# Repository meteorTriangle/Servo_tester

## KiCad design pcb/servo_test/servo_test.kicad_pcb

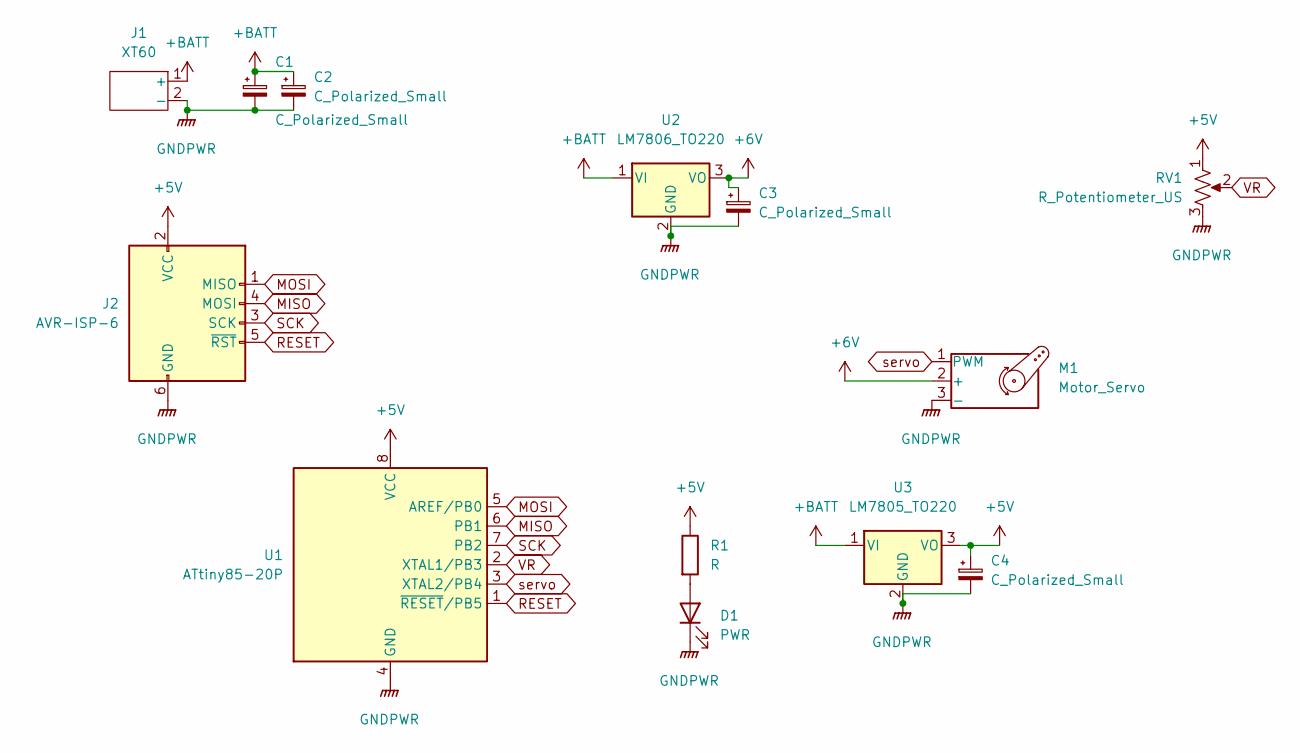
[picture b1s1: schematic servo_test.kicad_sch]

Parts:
C1, C2, C3, C4: C_Polarized_Small; CP_Radial_D5.0mm_P2.00mm
D1: PWR; LED_0805_2012Metric
J1: XT60; XT60_vertical_female
J2: AVR-ISP-6; PinHeader_2x03_P2.54mm_Vertical
M1: Motor_Servo; PinHeader_1x03_P2.54mm_Vertical
R1: R; R_0805_2012Metric
RV1: R_Potentiometer_US; Potentiometer_Piher_PC-16_Single_Horizontal
U1: ATtiny85-20P; DIP-8_W7.62mm
U2: LM7806_TO220; TO-220-3_Vertical
U3: LM7805_TO220; TO-220-3_Vertical

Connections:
+5V: C4.1, J2.2 (VCC), R1.1, RV1.1, U1.8 (VCC), U3.3 (VO)
+6V: C3.1, M1.2 (+), U2.3 (VO)
+BATT: C1.1, C2.1, J1.1 (+), U2.1 (VI), U3.1 (VI)
GNDPWR: C1.2, C2.2, C3.2, C4.2, D1.1 (K), J1.2 (-), J2.6 (GND), M1.3 (-), RV1.3, U1.4 (GND), U2.2 (GND), U3.2 (GND)
MISO: J2.4 (MOSI), U1.6 (PB1)
MOSI: J2.1 (MISO), U1.5 (AREF/PB0)
unnamed: D1.2 (A), R1.2
RESET: J2.5 (~RST), U1.1 (~RESET/PB5)
SCK: J2.3 (SCK), U1.7 (PB2)
VR: RV1.2, U1.2 (XTAL1/PB3)
servo: M1.1 (PWM), U1.3 (XTAL2/PB4)

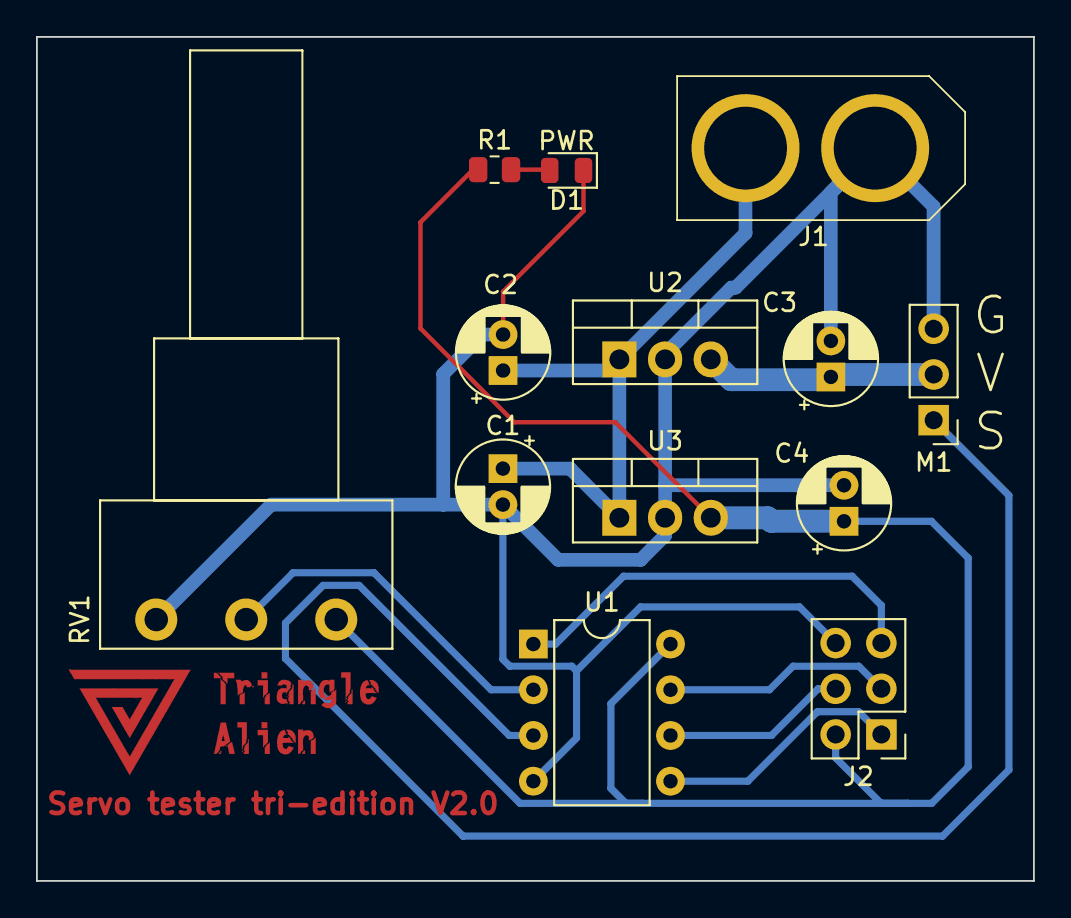
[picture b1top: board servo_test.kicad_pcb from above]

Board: 2 copper layers, 55.4 x 46.9 mm, 13 parts (0 on the bottom side), 11 nets.

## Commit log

2022-10-09 servo_tester v2.1
2022-10-23 case
